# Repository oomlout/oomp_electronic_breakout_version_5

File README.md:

<!-- oomp-documentation:start -->
# OOMP electronic breakouts

## Summary

Breakout boards, pin layouts and mounting geometry.

Representative example: Electronic Breakout Input Remote Control Servo Tester 18 Mm Width 14 Mm Height Purple Pcb Aliexpress. Other variants differ.

## Details

[OOMP version 5 directory](https://github.com/oomlout/oomlout_oomp_version_5) · [Generator and maintenance guide](README_GENERATOR.md)

## Parts

Browse **105 records** in the [part folders](parts/).

## Assembly

Choose an exact record before using its files. Installation and compatibility depend on the selected component; refer to its technical notes.
<!-- oomp-documentation:end -->

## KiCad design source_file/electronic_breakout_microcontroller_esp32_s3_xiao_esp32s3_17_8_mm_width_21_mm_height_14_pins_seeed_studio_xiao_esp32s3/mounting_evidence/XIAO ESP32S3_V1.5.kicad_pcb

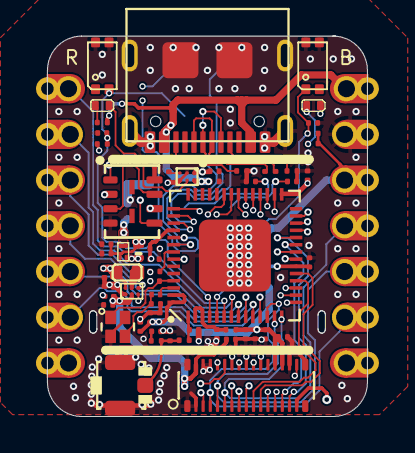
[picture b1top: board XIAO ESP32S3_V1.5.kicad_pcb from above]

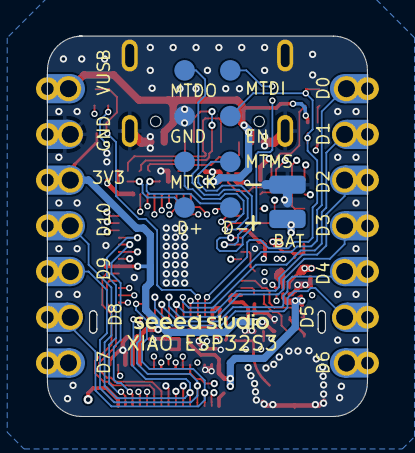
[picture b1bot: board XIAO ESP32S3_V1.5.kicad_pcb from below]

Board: 4 copper layers, 17.8 x 21.1 mm, 70 parts (10 on the bottom side), 62 nets.

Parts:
ANT1: U.FL-R-SMT-1; U-FL3P-SMD-2.6X2.6X1.0MM
BAT0: VBAT; TP-80X40MIL
C1, C2, C17, C20: DNP; C0201
C3, C9, C13, C16: 2.2uF; C0201
C4, C5, C6: 4.7uF; C0201
C7, C8, C28: 10pF; C0201
C10, C21, C25, C26: 1uF; C0201
C11, C14, C15, C19, C22, C23, C29, C30: 100nF; C0201
C12: 10nF; C0201
C18: 1pF; C0201
CHG0: RED; LED-0402
D2: LMBR4010BST5G; DFN1006-2L
D3: Yellow; LED-0402
GND0: GND; TP-80X40MIL
J3: DF40C-30DP-0.4V(51); BTB30-0.4-7.52X2.97X1.14
K1, K2: SKTAAAE010/311021459; SW4-SMD-2.8-2.6X1.6X0.53MM
L1: 2nH; L0201
L2: 3.3nH; L0201
L3: DNP; L0201
L4: 470nH; L0603
L5: 24nH; L0201
Q1: LP0404N3T5G; PMOS_1.0_0.6_0.35MM
R1, R2: 5.1K; R0201
R3, R4: 22R; R0201
R6: 499R; R0201
R7, R8, R11: 10K; R0201
R9: 100K; C0201
R10: 220K; R0201
R13: 249K; R0201
R15: 1.5K; R0201
TP1, TP2, TP3, TP4, TP5, TP6, TP7, TP8: TEST-POINT'4545'; TP-D45MIL
U1: ESP32-S3R8; QFN56G-0.4-7X7MM
U3: SGM6029CYG/TR; BGA6-0.35-0.745X10.95X0.4MM
U4: SGM40567-4.2XG/TR; WLCSP-0.4-0.92X1.16X0.4MM
U5: GD25Q64ENIGR; USON8-0.8-4X3MM
U9: XIAO-Add-On; XIAO-14P-Add-On
USB0: UBF31-0171; USB2.0-TYPE-C
X1: 40MHz/306011364; X4-SMD-1.6X1.2X0.35MM

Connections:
/03 XIAO ESP32-S3-Sense/D0/A0: U1.6 (GPIO1), U9.1 (D0)
/03 XIAO ESP32-S3-Sense/D1/A1: U1.7 (GPIO2), U9.2 (D1)
/03 XIAO ESP32-S3-Sense/D2/A2: J3.2, U1.8 (GPIO3), U9.3 (D2)
/03 XIAO ESP32-S3-Sense/D3/A3: U1.9 (GPIO4), U9.4 (D3)
/03 XIAO ESP32-S3-Sense/D4/I2C_SDA: U1.10 (GPIO5), U9.5 (D4)
/03 XIAO ESP32-S3-Sense/D5/I2C_SCL: U1.11 (GPIO6), U9.6 (D5)
/03 XIAO ESP32-S3-Sense/D6/TX: R6.2, U9.7 (D6)
/03 XIAO ESP32-S3-Sense/D7/RX: U1.50 (U0RXD), U9.8 (D7)
/03 XIAO ESP32-S3-Sense/D8/A8/SCK: J3.3, U1.12 (GPIO7), U9.9 (D8)
/03 XIAO ESP32-S3-Sense/D9/A9/MISO: J3.4, U1.13 (GPIO8), U9.10 (D9)
/03 XIAO ESP32-S3-Sense/D10/A10/MOSI: J3.5, U1.14 (GPIO9), U9.11 (D10)
/03 XIAO ESP32-S3-Sense/EN: C21.2, K1.1 (A0), K1.3 (A1), R8.1, TP6.T, U1.4 (CHIP_PU)
/03 XIAO ESP32-S3-Sense/ESP_USB_D+: C1.2, R4.2, TP8.T, U1.26 (GPIO20)
/03 XIAO ESP32-S3-Sense/ESP_USB_D-: C2.2, R3.2, TP7.T, U1.25 (GPIO19)
/03 XIAO ESP32-S3-Sense/GPIO0: C28.2, K2.1 (A0), K2.3 (A1), R7.1, U1.5 (GPIO0)
/03 XIAO ESP32-S3-Sense/IO10/XMCLK: J3.6, U1.15 (GPIO10)
/03 XIAO ESP32-S3-Sense/IO11/DVP_Y8: J3.7, U1.16 (GPIO11)
/03 XIAO ESP32-S3-Sense/IO12/DVP_Y7: J3.8, U1.17 (GPIO12)
/03 XIAO ESP32-S3-Sense/IO13/DVP_PCLK: J3.9, U1.18 (GPIO13)
/03 XIAO ESP32-S3-Sense/IO14/DVP_Y6: J3.10, U1.19 (GPIO14)
/03 XIAO ESP32-S3-Sense/IO15/DVP_Y2: J3.11, U1.21 (XTAL_32K_P)
/03 XIAO ESP32-S3-Sense/IO16/DVP_Y5: J3.12, U1.22 (XTAL_32K_N)
/03 XIAO ESP32-S3-Sense/IO17/DVP_Y3: J3.13, U1.23 (GPIO17)
/03 XIAO ESP32-S3-Sense/IO18/DVP_Y4: J3.14, U1.24 (GPIO18)
/03 XIAO ESP32-S3-Sense/IO21/USER_LED: D3.-, J3.16, U1.27 (GPIO21)
/03 XIAO ESP32-S3-Sense/IO38/DVP_VSYNC: J3.23, U1.43 (GPIO38)
/03 XIAO ESP32-S3-Sense/IO47/DVP_HREF: J3.22, U1.37 (SPICLK_P)
/03 XIAO ESP32-S3-Sense/IO48/DVP_Y9: J3.21, U1.36 (SPICLK_N)
/03 XIAO ESP32-S3-Sense/MTCK/IO39/CAM_SCL: J3.24, TP5.T, U1.44 (MTCK)
/03 XIAO ESP32-S3-Sense/MTDI/IO41/PDM_DATA: J3.26, TP3.T, U1.47 (MTDI)
/03 XIAO ESP32-S3-Sense/MTDO/IO40/CAM_SDA: J3.25, TP4.T, U1.45 (MTDO)
/03 XIAO ESP32-S3-Sense/MTMS/IO42/PDM_CLK: J3.27, TP2.T, U1.48 (MTMS)
/03 XIAO ESP32-S3-Sense/SPICLK: U1.33 (SPICLK), U5.6 (CLK)
/03 XIAO ESP32-S3-Sense/SPICS0: U1.32 (SPICS0), U5.1 (/CS)
/03 XIAO ESP32-S3-Sense/SPID: U1.35 (SPID), U5.5 (DIO)
/03 XIAO ESP32-S3-Sense/SPIHD: U1.30 (SPIHD), U5.7 (/HOLD)
/03 XIAO ESP32-S3-Sense/SPIQ: U1.34 (SPIQ), U5.2 (DO)
/03 XIAO ESP32-S3-Sense/SPIWP: U1.31 (SPIWP), U5.3 (/WP)
/03 XIAO ESP32-S3-Sense/USB_D+: R4.1, USB0.A6 (A6/DP1), USB0.B6 (B6/DP2)
/03 XIAO ESP32-S3-Sense/USB_D-: R3.1, USB0.A7 (A7/DN1), USB0.B7 (B7/DN2)
/03 XIAO ESP32-S3-Sense/VBAT: BAT0.1 (T), C26.1, Q1.1 (D), U4.A1 (BAT)
/03 XIAO ESP32-S3-Sense/VBUS: C10.1, C25.1, D2.+, Q1.2 (G), R9.2, R11.1, U4.A2 (VIN), U9.14 (VBUS), USB0.A4_B9 (A4/B9/VBUS), USB0.B4_A9 (B4/A9/VBUS)
/03 XIAO ESP32-S3-Sense/VCC_3V3: C5.2, C6.2, C9.2, C11.2, C12.2, C13.2, C14.2, C16.2, C19.2, C23.1, C29.2, J3.18, J3.19, L1.1, L4.2, R7.2, R8.2, R15.2, U1.20 (VDD3P3_RTC), U1.46 (VDD3P3_CPU), U1.55 (VDDA@1), U1.56 (VDDA@2), U3.A2 (VOS), U9.12 (3V3_OUT)
/03 XIAO ESP32-S3-Sense/VDD_SPI: C22.2, U1.29 (VDD_SPI), U5.8 (VCC)
/03 XIAO ESP32-S3-Sense/VIN: C3.1, C4.1, C30.2, D2.-, J3.15, J3.30, Q1.3 (S), U3.B1 (VIN), U3.C2 (EN)
GND: ANT1.GND1, ANT1.GND2, C1.1, C2.1, C3.2, C4.2, C5.1, C6.1, C7.2, C8.1, C9.1, C10.2, C11.1, C12.1, C13.1, C14.1, C15.1, C16.1, C17.1, C18.1, C19.1, C20.1, C21.1, C22.1, C23.2, C25.2, C26.2, C28.1, C29.1, C30.1, GND0.1 (T), J3.1, J3.17, J3.28, J3.29, J3.31, J3.33, J3.34, K1.2 (B0), K1.4 (B1), K2.2 (B0), K2.4 (B1), R1.1, R2.2, R9.1, R10.1, R13.1, TP1.T, U1.57 (GND), U3.A1 (GND), U4.B1 (F), U4.C2 (GND), U5.4 (GND), U9.13 (GND), USB0.A1_B12 (A1/B12/GND), USB0.B1_A12 (B1/A12/GND), USB0.S1, USB0.S2, USB0.S3, USB0.S4, USB0.S5 (S1), USB0.S6 (S2), X1.2 (GND), X1.4 (GND@1)
unnamed: ANT1.D, C17.2, L2.1, L3.2
unnamed: C20.2, L3.1
unnamed: CHG0.+, R11.2
unnamed: D3.+, R15.1
unnamed: C18.2, L2.2, U1.1 (LNA_IN)
unnamed: R6.1, U1.49 (U0TXD)
unnamed: C15.2, L1.2, U1.2 (VDD3P3@1), U1.3 (VDD3P3@2)
unnamed: C8.2, U1.53 (XTAL_N), X1.1 (X1)
unnamed: L5.1, U1.54 (XTAL_P)
unnamed: R13.2, U3.C1 (MODE)
unnamed: L4.1, U3.B2 (SW)
unnamed: R10.2, U4.C1 (IREF)
unnamed: CHG0.-, U4.B2 (NCHG)
unnamed: R1.2, USB0.A5 (A5/CC1)
unnamed: R2.1, USB0.B5 (B5/CC2)
unnamed: C7.1, L5.2, X1.3 (X2)

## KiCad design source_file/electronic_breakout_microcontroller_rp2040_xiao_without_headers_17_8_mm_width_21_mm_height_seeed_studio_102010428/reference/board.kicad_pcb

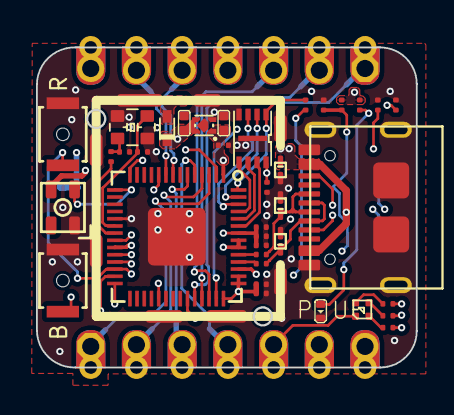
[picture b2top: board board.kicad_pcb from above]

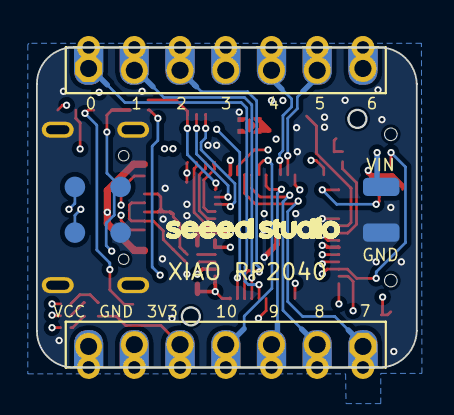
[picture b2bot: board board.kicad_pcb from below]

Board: 4 copper layers, 21.1 x 17.8 mm, 47 parts (7 on the bottom side), 44 nets.

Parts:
BOOT0: BUTTON_TD1183SA
C2, C3, C7, C10, C15, C18, C21: 100nF; 0201_NORMAL_NOSILK
C5, C6: 10uF; C0402
C16: 1uF; 0201_NORMAL_NOSILK
C19, C20: 18pF; 0201_NORMAL_NOSILK
D1, D8, D9: DF2S6.8FS; SOD-923
D2: NRS0320MW2T1G; SOD523
GND0: TEST-POINT'4080'; TP-80X40MIL
J1: SHIELDING-COVER-XIAO_RP2040_PRD; SHIELDING-COVER_XIAO_RP2040_PRD
J2, J4: DNP; H7-HALF-HOLE-2.54
PWR0: RED; LED-0402
R1, R2: 5.1k; R0201
R3: 2.2K; R0201
R4: 4.7K; R0201
R5: 10k; R0201
R6, R14, R24: 1k; R0201
R7: 11K; R0201
R22, R23: 27R; R0201
RESET0: BUTTON_TD1183SA
RGB1: LED_RGB_4P; LED_RGB_2427
RGB2: LED_RGB_4P-1010; 1010-4P
TP1, TP3, TP5, TP6: TEST-POINT'4545'; TP-D45MIL
U3: FLASH_P25Q16SH_USON8_3X2MM; FLASH_GD25Q16CEIG_2_GD25Q16CEIG_USON8_3X2MM
U4: LDO_DFN11_4P; LDO_DFN1_1_4P
U6: RP2040_QFN56
U$4: LOGO-SEEED-NEW-1X9.6MM
USB1: USB2.0-TYPE-C
VIN0: TEST-POINT'4080'; TP-80X40MIL
X3: CRYSTAL_4P_2520

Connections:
/02 SAMD21/1V1: C15.1, C16.1, C18.1, U6.23 (DVDD@1), U6.45 (VREG_VOUT), U6.50 (DVDD@2)
/02 SAMD21/3V3: C3.1, C6.2, C7.1, C10.1, C21.2, J4.5, J4.17 (5), R5.1, R6.1, RGB2.+, U3.8 (VCC), U4.1 (VOUT), U6.1 (IOVDD@1), U6.10 (IOVDD@2), U6.22 (IOVDD@3), U6.33 (IOVDD@4), U6.42 (IOVDD@5), U6.43 (ADC_IOVDD), U6.44 (VREG_IOVDD), U6.48 (USB_IOVDD), U6.49 (IOVDD@6)
/02 SAMD21/A0: J2.1, J2.13 (1), U6.38 (GPIO26/ADC0)
/02 SAMD21/A1: J2.2, J2.14 (2), U6.39 (GPIO27/ADC1)
/02 SAMD21/A2: J2.3, J2.15 (3), U6.40 (GPIO28/ADC2)
/02 SAMD21/A3: J2.4, J2.16 (4), U6.41 (GPIO29/ADC3)
/02 SAMD21/IO16_RGB-G: R7.2, U6.27 (GPIO16)
/02 SAMD21/IO17_RGB-R: R4.2, U6.28 (GPIO17)
/02 SAMD21/IO25_RGB-B: R3.2, U6.37 (GPIO25)
/02 SAMD21/MISO: J4.3, J4.15 (3), U6.6 (GPIO4)
/02 SAMD21/MOSI: J4.4, J4.16 (4), U6.5 (GPIO3)
/02 SAMD21/NEOPIX: RGB1.3 (DIN), U6.15 (GPIO12)
/02 SAMD21/NEO_PWR: RGB1.4 (VCC), U6.14 (GPIO11)
/02 SAMD21/QSPI_CSN: R14.2, U3.1 (CS), U6.56 (QSPI_CS)
/02 SAMD21/QSPI_SCK: U3.6 (SCLK), U6.52 (QSPI_SCLK)
/02 SAMD21/QSPI_SIO_0: U3.5 (SI), U6.53 (QSPI_SDO)
/02 SAMD21/QSPI_SIO_1: U3.2 (SO), U6.55 (QSPI_SD1)
/02 SAMD21/QSPI_SIO_2: U3.3 (WP), U6.54 (QSPI_SD2)
/02 SAMD21/QSPI_SIO_3: U3.7 (HOLD), U6.51 (QSPI_SD3)
/02 SAMD21/RP2040_BOOT: BOOT0.1, R14.1
/02 SAMD21/RUN: C2.1, R5.2, RESET0.1, TP1.T, U6.26 (RUN)
/02 SAMD21/RX: J4.1, J4.13 (1), U6.3 (GPIO1)
/02 SAMD21/SCK: J4.2, J4.14 (2), U6.4 (GPIO2)
/02 SAMD21/SCL: J2.6, J2.18 (6), U6.9 (GPIO7)
/02 SAMD21/SDA: J2.5, J2.17 (5), U6.8 (GPIO6)
/02 SAMD21/SWDCLK: TP3.T, U6.24 (SWCLK)
/02 SAMD21/SWDIO: TP5.T, U6.25 (SWDIO)
/02 SAMD21/TX: J2.7, J2.19 (7), U6.2 (GPIO0)
/02 SAMD21/USB_D+: D8.1 (2), R23.2, USB1.A6 (A6/DP1), USB1.B6 (B6/DP2)
/02 SAMD21/USB_D-: D9.1 (2), R22.2, USB1.A7 (A7/DN1), USB1.B7 (B7/DN2)
/02 SAMD21/USB_DM: R22.1, U6.46 (USB_DM)
/02 SAMD21/USB_DP: R23.1, U6.47 (USB_DP)
/02 SAMD21/VBUS: D1.1 (2), D2.A, J4.7, J4.19 (7), USB1.A4_B9 (A4/B9/VBUS), USB1.B4_A9 (B4/A9/VBUS)
/02 SAMD21/XIN: C19.2, U6.20 (XIN), X3.1
/02 SAMD21/XOUT: R24.2, U6.21 (XOUT)
GND: BOOT0.2, C2.2, C3.2, C5.1, C6.1, C7.2, C10.2, C15.2, C16.2, C18.2, C19.1, C20.2, C21.1, D1.2 (1), D8.2 (1), D9.2 (1), GND0.1 (T), J1.1, J1.2, J1.3, J1.4, J1.5, J1.6, J1.7, J1.8, J4.6, J4.18 (6), PWR0.-, R1.2, R2.1, RESET0.2, RGB1.2 (VSS), TP6.T, U3.4 (VSS), U3.9 (GND), U4.2 (GND), U4.5 (EP), U6.19 (TESTEN), U6.57 (GND), USB1.A1_B12 (A1/B12/GND), USB1.B1_A12 (B1/A12/GND), USB1.S1, USB1.S2, USB1.S3, USB1.S4, USB1.S5 (S1), USB1.S6 (S2), X3.2, X3.4
unnamed: C20.1, R24.1, X3.3
unnamed: PWR0.+, R6.2
unnamed: R3.1, RGB2.B-
unnamed: R4.1, RGB2.R-
unnamed: R7.1, RGB2.G-
unnamed: C5.2, D2.C, U4.3 (CE), U4.4 (VIN), VIN0.1 (T)
unnamed: R1.1, USB1.A5 (A5/CC1)
unnamed: R2.2, USB1.B5 (B5/CC2)

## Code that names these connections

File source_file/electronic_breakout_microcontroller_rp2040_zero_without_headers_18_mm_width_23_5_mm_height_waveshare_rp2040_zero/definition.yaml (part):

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  left_4:
    connector: left
    number: '4'
    name: GPIO29
    gpio: 29
    adc_channel: 3
    chip_pin_number: '41'
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  left_5:
    connector: left
    number: '5'
    name: GPIO28
    gpio: 28
    adc_channel: 2
    chip_pin_number: '40'
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  left_6:
    connector: left
    number: '6'
    name: GPIO27
    gpio: 27
    adc_channel: 1
    chip_pin_number: '39'
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  left_7:
    connector: left
    number: '7'
    name: GPIO26
    gpio: 26
    adc_channel: 0
    chip_pin_number: '38'
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  left_9:
    connector: left
    number: '9'
    name: GPIO14
    gpio: 14
    adc_channel: null
    chip_pin_number: '17'
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  right_1:
    connector: right
    number: '1'
    name: GPIO0
    gpio: 0
    adc_channel: null
    chip_pin_number: '2'
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  right_2:
    connector: right
    number: '2'
    name: GPIO1
    gpio: 1
    adc_channel: null
    chip_pin_number: '3'
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  right_3:
    connector: right
    number: '3'
    name: GPIO2
    gpio: 2
    adc_channel: null
    chip_pin_number: '4'
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  right_4:
    connector: right
    number: '4'
    name: GPIO3
    gpio: 3
    adc_channel: null
    chip_pin_number: '5'
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  right_5:
    connector: right
    number: '5'
    name: GPIO4
    gpio: 4
    adc_channel: null
    chip_pin_number: '6'
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  right_6:
    connector: right
    number: '6'
    name: GPIO5
    gpio: 5
    adc_channel: null
    chip_pin_number: '7'
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  right_7:
    connector: right
    number: '7'
    name: GPIO6
    gpio: 6
    adc_channel: null
    chip_pin_number: '8'
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  right_8:
    connector: right
    number: '8'
    name: GPIO7
    gpio: 7
    adc_channel: null
    chip_pin_number: '9'
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  right_9:
    connector: right
    number: '9'
    name: GPIO8
    gpio: 8
    adc_channel: null
    chip_pin_number: '11'
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  bottom_1:
    connector: bottom
    number: '1'
    name: GPIO13
    gpio: 13
    adc_channel: null
    chip_pin_number: '16'
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  bottom_2:
    connector: bottom
    number: '2'
    name: GPIO12
    gpio: 12
    adc_channel: null
    chip_pin_number: '15'
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  bottom_3:
    connector: bottom
    number: '3'
    name: GPIO11
    gpio: 11
    adc_channel: null
    chip_pin_number: '14'
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  bottom_4:
    connector: bottom
    number: '4'
    name: GPIO10
    gpio: 10
    adc_channel: null
    chip_pin_number: '13'
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  bottom_5:
    connector: bottom
    number: '5'
    name: GPIO9
    gpio: 9
    adc_channel: null
    chip_pin_number: '12'
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  underside_GP17:
    connector: underside
    number: GP17
    name: GPIO17
    gpio: 17
    adc_channel: null
    chip_pin_number: '28'
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  underside_GP18:
    connector: underside
    number: GP18
    name: GPIO18
    gpio: 18
    adc_channel: null
    chip_pin_number: '29'
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  underside_GP19:
    connector: underside
    number: GP19
    name: GPIO19
    gpio: 19
    adc_channel: null
    chip_pin_number: '30'
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  underside_GP20:
    connector: underside
    number: GP20
    name: GPIO20
    gpio: 20
    adc_channel: null
    chip_pin_number: '31'
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  underside_GP21:
    connector: underside
    number: GP21
    name: GPIO21
    gpio: 21
    adc_channel: null
    chip_pin_number: '32'
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  underside_GP25:
    connector: underside
    number: GP25
    name: GPIO25
    gpio: 25
    adc_channel: null
    chip_pin_number: '37'
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
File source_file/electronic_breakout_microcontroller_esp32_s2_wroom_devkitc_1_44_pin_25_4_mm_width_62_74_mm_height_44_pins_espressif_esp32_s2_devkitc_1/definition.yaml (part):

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    source_id: board_guide
    functions:
    - RTC_GPIO4
    - GPIO4
    - TOUCH4
    - ADC1_CH3
    manufacturer_pin_type: I/O/T
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    source_id: board_guide
    functions:
    - RTC_GPIO5
    - GPIO5
    - TOUCH5
    - ADC1_CH4
    manufacturer_pin_type: I/O/T
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    source_id: board_guide
    functions:
    - RTC_GPIO6
    - GPIO6
    - TOUCH6
    - ADC1_CH5
    manufacturer_pin_type: I/O/T
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    source_id: board_guide
    functions:
    - RTC_GPIO7
    - GPIO7
    - TOUCH7
    - ADC1_CH6
    manufacturer_pin_type: I/O/T
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    source_id: board_guide
    functions:
    - RTC_GPIO16
    - GPIO16
    - U0CTS
    - ADC2_CH5
    - XTAL_32K_N
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    source_id: board_guide
    functions:
    - RTC_GPIO17
    - GPIO17
    - U1TXD
    - ADC2_CH6
    - DAC_1
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    source_id: board_guide
    functions:
    - RTC_GPIO18
    - GPIO18
    - U1RXD
    - ADC2_CH7
    - DAC_2
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    source_id: board_guide
    functions:
    - RTC_GPIO8
    - GPIO8
    - TOUCH8
    - ADC1_CH7
    manufacturer_pin_type: I/O/T
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    source_id: board_guide
    functions:
    - RTC_GPIO3
    - GPIO3
    - TOUCH3
    - ADC1_CH2
    manufacturer_pin_type: I/O/T
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    source_id: board_guide
    functions:
    - RTC_GPIO9
    - GPIO9
    - TOUCH9
    - ADC1_CH8
    - FSPIHD
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    source_id: board_guide
    functions:
    - RTC_GPIO10
    - GPIO10
    - TOUCH10
    - ADC1_CH9
    - FSPICS0
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    source_id: board_guide
    functions:
    - RTC_GPIO11
    - GPIO11
    - TOUCH11
    - ADC2_CH0
    - FSPID
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    source_id: board_guide
    functions:
    - RTC_GPIO12
    - GPIO12
    - TOUCH12
    - ADC2_CH1
    - FSPICLK
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    source_id: board_guide
    functions:
    - RTC_GPIO13
    - GPIO13
    - TOUCH13
    - ADC2_CH2
    - FSPIQ
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    source_id: board_guide
    functions:
    - RTC_GPIO14
    - GPIO14
    - TOUCH14
    - ADC2_CH3
    - FSPIWP
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    source_id: board_guide
    functions:
    - RTC_GPIO1
    - GPIO1
    - TOUCH1
    - ADC1_CH0
    manufacturer_pin_type: I/O/T
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    source_id: board_guide
    functions:
    - RTC_GPIO2
    - GPIO2
    - TOUCH2
    - ADC1_CH1
    manufacturer_pin_type: I/O/T
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    y_mm: -7.24
    source_id: board_guide
    functions:
    - GPIO38
    - FSPIWP
    manufacturer_pin_type: I/O/T
    position_source_id: mechanical
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    source_id: board_guide
    functions:
    - RTC_GPIO0
    - GPIO0
    manufacturer_pin_type: I/O/T
    position_source_id: mechanical
    restrictions:
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    source_id: board_guide
    functions:
    - RTC_GPIO21
    - GPIO21
    manufacturer_pin_type: I/O/T
    position_source_id: mechanical
    restrictions: []
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    source_id: board_guide
    functions:
    - RTC_GPIO20
    - GPIO20
    - U1CTS
    - ADC2_CH9
    - CLK_OUT1
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    source_id: board_guide
    functions:
    - RTC_GPIO19
    - GPIO19
    - U1RTS
    - ADC2_CH8
    - CLK_OUT2
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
